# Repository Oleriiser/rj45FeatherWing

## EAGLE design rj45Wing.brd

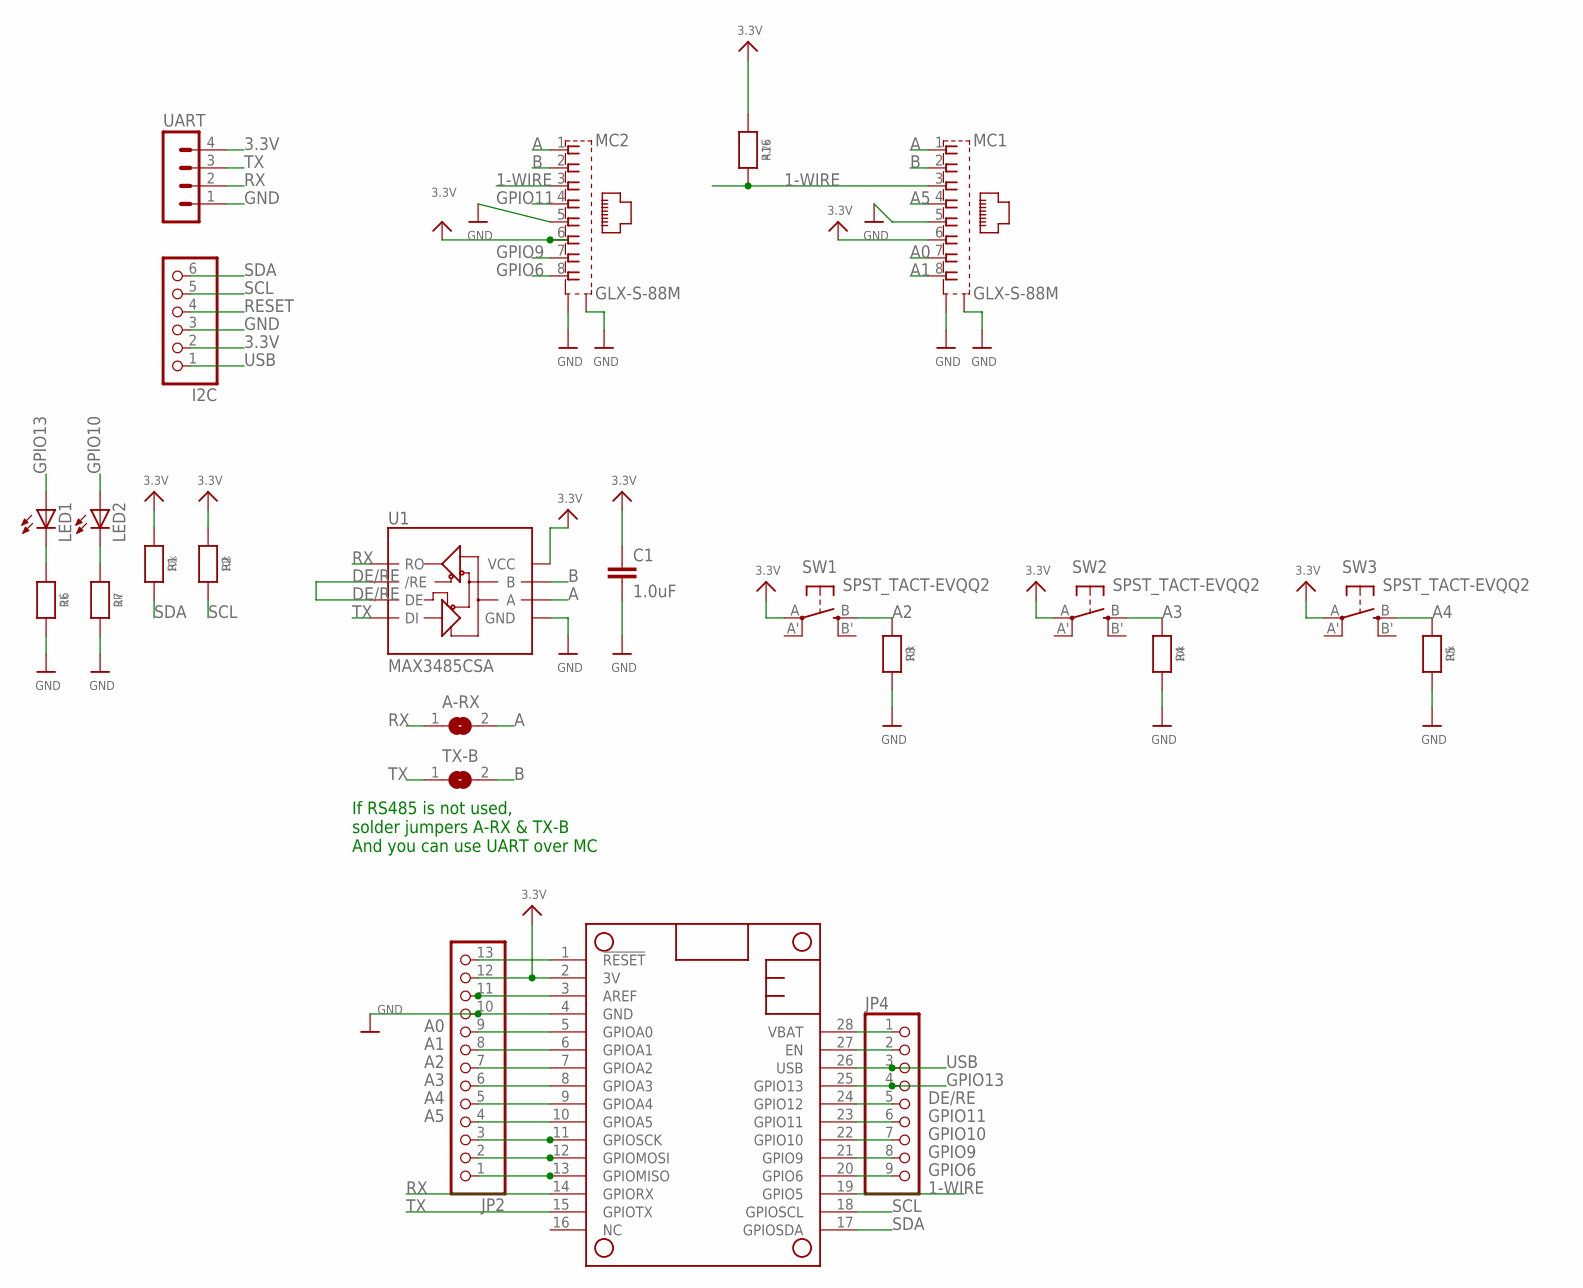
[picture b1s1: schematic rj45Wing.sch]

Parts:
A-RX: SJ
C1: 1.0uF; 0402
I2C: PINHD-1X6; 1X06
JP2: HEADER-1X13; 1X13_ROUND_70
JP4: HEADER-1X970MIL; 1X09_ROUND_70
LED1, LED2: LEDCHIP-LED0805; CHIP-LED0805
MC1, MC2: GLX-S-88M
MS1: FEATHERWING_NODIM
R1, R2, R3, R4, R5: 10k; 0603-NO
R6, R7: 2k; 0603-NO
R16: 4.7k; 0603-NO
SW1, SW2, SW3: SPST_TACT-EVQQ2; EVQ-Q2
TX-B: SJ
U1: MAX3485CSA; SO08
UART: MA04-1

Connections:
1-WIRE: MC1.3, MC2.3, MS1.19 (GPIO5), R16.2
3.3V: C1.1, I2C.2, JP2.12, MC1.6, MC2.6, MS1.2 (3V), R1.1, R2.1, R16.1, SW1.A, SW2.A, SW3.A, U1.8 (VCC), UART.4
A: A-RX.2, MC1.1, MC2.1, U1.6 (A)
A0: JP2.9, MC1.7, MS1.5 (GPIOA0)
A1: JP2.8, MC1.8, MS1.6 (GPIOA1)
A2: JP2.7, MS1.7 (GPIOA2), R3.1, SW1.B (S)
A3: JP2.6, MS1.8 (GPIOA3), R4.1, SW2.B (S)
A4: JP2.5, MS1.9 (GPIOA4), R5.1, SW3.B (S)
A5: JP2.4, MC1.4, MS1.10 (GPIOA5)
B: MC1.2, MC2.2, TX-B.2, U1.7 (B)
DE/RE: JP4.5, MS1.24 (GPIO12), U1.2 (/RE), U1.3 (DE)
GND: C1.2, I2C.3, JP2.10, MC1.5, MC1.S1, MC1.S2, MC2.5, MC2.S1, MC2.S2, MS1.4 (GND), R3.2, R4.2, R5.2, R6.2, R7.2, U1.5 (GND), UART.1
GPIO6: JP4.9, MC2.8, MS1.20 (GPIO6)
GPIO9: JP4.8, MC2.7, MS1.21 (GPIO9)
GPIO10: JP4.7, LED2.A, MS1.22 (GPIO10)
GPIO11: JP4.6, MC2.4, MS1.23 (GPIO11)
GPIO13: JP4.4, LED1.A, MS1.25 (GPIO13)
MISO_MCU: JP2.1, MS1.13 (GPIOMISO)
MOSI: JP2.2, MS1.12 (GPIOMOSI)
unnamed: LED1.C, R6.1
unnamed: LED2.C, R7.1
unnamed: JP4.2, MS1.27 (EN)
unnamed: JP2.13, MS1.1 (!RESET)
unnamed: JP2.11, MS1.3 (AREF)
RESET: I2C.4
RX: A-RX.1, MS1.14 (GPIORX), U1.1 (RO), UART.2
SCK: JP2.3, MS1.11 (GPIOSCK)
SCL: I2C.5, MS1.18 (GPIOSCL), R2.2
SDA: I2C.6, MS1.17 (GPIOSDA), R1.2
TX: MS1.15 (GPIOTX), TX-B.1, U1.4 (DI), UART.3
USB: I2C.1, JP4.3, MS1.26 (USB)
VBAT: JP4.1, MS1.28 (VBAT)

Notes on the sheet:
If RS485 is not used, solder jumpers A-RX & TX-B And you can use UART over MC

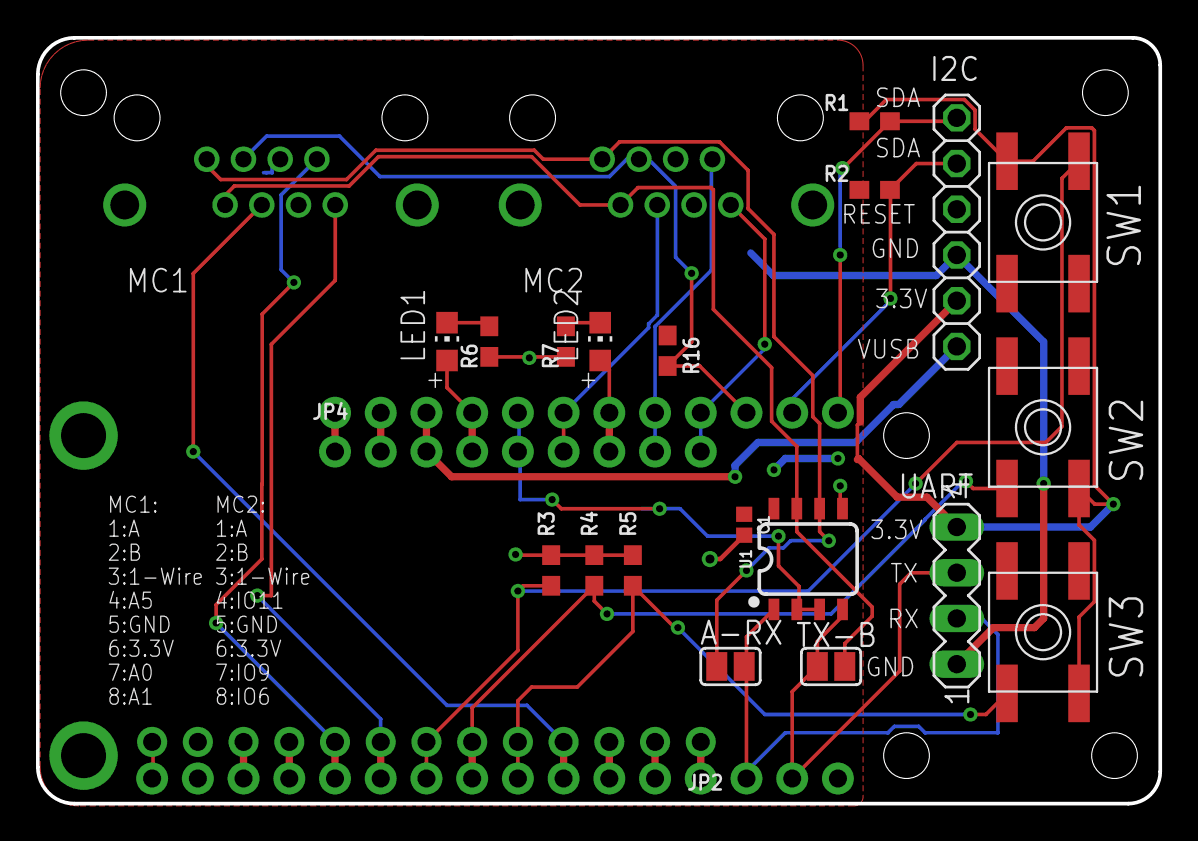
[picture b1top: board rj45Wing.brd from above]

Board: 2 copper layers, 62.4 x 42.5 mm, 24 parts (0 on the bottom side), 31 nets.

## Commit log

2020-03-23 added files
2020-04-06 first route
2020-04-06 added schematic
2020-04-07 replaced rj45 connector
2020-04-07 added gerber
2020-04-07 new RJ45 terminals
2020-04-07 added board image
2020-07-11 added cap close to rs458 ic

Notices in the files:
parts and their libraries:
microbuilder: This work is placed in the public domain, and may be freely used for commercial and non-commercial work with the following conditions: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
SparkFun-IC-Comms: Licensing: Creative Commons ShareAlike 4.0 International - https://creativecommons.org/licenses/by-sa/4.0
